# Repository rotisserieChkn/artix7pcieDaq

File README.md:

## About

WORK IN PROGRESS

Right now, only the KiCAD pcb files have been added to the repo. The HDL and PC side software used to communicate with the PCB over PCIe have not been added yet. Stay tuned!

## Licensing

This repository contains hardware, software, and HDL components
that are licensed separately.

### Hardware

All original hardware design files in the `hardware/`
directory are licensed under the CERN Open Hardware
License Version 2 - Weakly Reciprocal (CERN-OHL-W-2.0).

### Software and HDL

All original firmware source code in the `software/` and `hdl/`
directories are licensed under the Mozilla Public License
2.0 (MPL-2.0).

### Third-party components

Third-party components retain their respective original
licenses. See their accompanying license notices where
applicable.

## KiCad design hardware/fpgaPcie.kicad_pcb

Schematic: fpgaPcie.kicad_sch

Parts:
C1, C7, C9, C23, C26, C32, C33, C54: 1210_47uF; C_1210_3225Metric
C2, C4, C6, C8, C13, C15, C19, C22, C24, C29, C31: 0603_100nF; C_0603_1608Metric
C3, C5, C14, C17, C30: 1210_10uF; C_1210_3225Metric
C10, C11, C12, C16, C18, C20, C21, C25, C27, C28: 0402_100nF; R_0402_1005Metric
C34, C35, C36, C39, C40, C41, C44, C45, C46, C49, C50, C51, C57, C58, C59, C60, C61, C62, C65, C66, C68, C70, C73, C74, C76, C77, C78: 0603_470nF; C_0603_1608Metric
C37, C38, C42, C43, C47, C48, C52, C53, C55, C56, C63, C64, C67, C69, C71, C72: 0805_4.7uF; C_0805_2012Metric
C75: 0603_50pF; C_0603_1608Metric
D1, D2, D3, D4: LED_0805; LED_0805_2012Metric
J1: PJ-002AH; MFG_PN PJ-002AH
J2: 6pinJTAG; PinHeader_1x06_P2.54mm_Vertical
J3: jumper_header; PinHeader_1x02_P2.54mm_Vertical
J4: jumper_header; 2x2_Header_100mil
J6: Bus_PCI_Express_x4; BUS_PCIexpress_x4
J7: TL3305AF260QG
J10: SMA_Connector; EMPCB.CSMAFSTJ.A
R1, R2, R8, R23, R24, R25, R26, R27, R34, R58, R60, R61, R62, R63: 0603_2k2; R_0603_1608Metric
R3, R4, R5, R6, R7, R14, R17, R30, R33, R38, R43, R51, R52, R64, R65: 0603_100R; R_0603_1608Metric
R9, R10, R20, R22, R28, R31, R41, R42, R48: 0603_10k; R_0603_1608Metric
R11, R12: 0603_6.65k; R_0603_1608Metric
R13, R15, R32, R35, R36, R45, R46: 0603_330k; R_0603_1608Metric
R16, R19, R40: 0603_71.5K; R_0603_1608Metric
R18, R21, R39, R53, R56: 0603_3.3K; R_0603_1608Metric
R29: 0603_20k; R_0603_1608Metric
R37, R47: 0603_34.8K; R_0603_1608Metric
R44, R66, R69: 0603_45.3k; R_0603_1608Metric
R49: 0603_220R; R_0603_1608Metric
R50: 0603_49R9; R_0603_1608Metric
R54: 0603_100k; R_0603_1608Metric
R55, R57: 0603_402R; R_0603_1608Metric
R59: RA_res_0603; R_0603_RA
R67: 0603_1k; R_0603_1608Metric
TP1: test_point; TP
U1, U2, U4, U5, U7: TPSM843521; QFN_FCMOD_9; MFG_PN TPSM843521RCJR
U3: XC7A35T-CSG325; Xilinx_CSG325; MFG_PN XC7A35T-CSG325
U6: 128MBIT-NOR; SOIC-16W_7.5x10.3mm_P1.27mm; MFG_PN S25FL128SAGMFI003
U8: 100MHz; ASEM1-100.000MHZ-LC-T; MFG_PN ASEM1-100.000MHZ-LC-T
U9: ADC3908S025; VQFN-32-1EP_4x4mm_P0.4mm_EP2.8x2.8mm_MODDED_PASTE; MFG_PN ADC3908S025IRSMT
U10: TPS7A2018PDBVR; SOT-23-5; MFG_PN TPS7A2018PDBVR
U11: THS4541IRGTR; VQFN-16-1EP_3x3mm_P0.5mm_EP1.45x1.45mm_CUSTOM_PASTE; MFG_PN THS4541IRGTR
X1: ECS-2520MV-200-CN-TR; 50_MHz_OSC; MFG_PN ECS-2520MV-200-CN-TR

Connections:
1V0_MGTAVCC: C8.1, C9.1, C56.1, C65.1, C66.1, C67.1, R12.2, U2.4 (VOUT), U3.B4 (MGTAVCC), U3.C5 (MGTAVCC), U3.E5 (MGTAVCC), U3.F5 (MGTAVCC)
1V0_VCCINT: C6.1, C7.1, C49.1, C50.1, C51.1, C52.1, C54.1, C60.1, C69.1, R11.2, U1.4 (VOUT), U3.F7 (VCCINT), U3.F9 (VCCINT), U3.F11 (VCCBRAM), U3.G8 (VCCINT), U3.G10 (VCCBRAM), U3.H7 (VCCINT), U3.H9 (VCCINT), U3.H11 (VCCBRAM), U3.J8 (VCCINT), U3.J12 (VCCINT), U3.K7 (VCCINT), U3.K11 (VCCINT), U3.L8 (VCCINT), U3.L12 (VCCINT), U3.M7 (VCCINT), U3.M11 (VCCINT), U3.N8 (VCCINT), U3.N10 (VCCINT), U3.N12 (VCCINT), U3.P9 (VCCINT), U3.P11 (VCCINT)
1V2_MGTAVTT: C24.1, C26.1, C61.1, C62.1, C63.1, C64.1, R31.2, R51.1, U3.A2 (MGTAVTT), U3.C1 (MGTAVTT), U3.E1 (MGTAVTT), U3.F3 (MGTAVTT), U3.G2 (MGTAVTT), U5.4 (VOUT)
1V8_ADC: C72.1, C73.1, C76.1, R58.1, U9.12 (AVDD), U9.13 (AVDD), U9.16 (M0), U10.5 (VOUT), X1.4 (VDD)
1V8_VCCAUX: C22.1, C23.1, C53.1, C55.1, C57.1, C58.1, C59.1, R29.2, U3.G12 (VCCAUX), U3.H13 (VCCAUX), U3.J10 (VCCADC_0), U3.K13 (VCCAUX), U3.M13 (VCCAUX), U3.P13 (VCCAUX), U4.4 (VOUT)
3V3_VCCIO: C1.1, C19.1, C31.1, C32.1, C33.1, C34.1, C35.1, C36.1, C37.1, C38.1, C39.1, C40.1, C41.1, C42.1, C43.1, C44.1, C45.1, C46.1, C47.1, C48.1, C68.1, C70.1, C71.1, C74.1, C77.1, J2.6 (VCC), R1.2, R2.2, R23.2, R24.2, R25.2, R26.2, R27.2, R34.2, R44.2, R49.2, U3.A16 (VCCO_15), U3.B13 (VCCO_15), U3.C10 (VCCO_15), U3.D17 (VCCO_15), U3.E10 (VCCO_0), U3.E12 (CFGBVS_0), U3.E14 (VCCO_15), U3.G18 (VCCO_15), U3.H15 (VCCO_15), U3.L6 (VCCO_34), U3.L16 (VCCO_14), U3.M3 (VCCO_34), U3.P7 (VCCO_34), U3.P17 (VCCO_14), U3.R4 (VCCO_34), U3.R10 (VCCO_0), U3.R14 (VCCO_14), U3.T1 (VCCO_34), U3.T11 (VCCO_14), U3.U8 (VCCO_14), U3.U18 (VCCO_14), U3.V5 (VCCO_34), U3.V15 (VCCO_14), U6.2 (VCC), U7.4 (VOUT), U8.4 (VDD), U9.27 (IOVDD), U10.1 (VIN), U10.3 (ENA), U11.5 (VS+), U11.6 (VS+), U11.7 (VS+), U11.8 (VS+), U11.12 (~PD); also elsewhere on the board
12V_VIN: C2.1, C3.1, C4.1, C5.1, C13.1, C14.1, C15.1, C17.1, C29.1, C30.1, J1.1, R9.2, R10.2, R28.2, U1.6 (VIN), U2.6 (VIN), U4.6 (VIN), U5.6 (VIN), U7.6 (VIN)
/ADC_CLK_GEN: R59.1, U3.N18 (IO_L10P_T1_D14_14)
/ADC_D0: U3.C14 (IO_L9P_T1_DQS_AD3P_15), U9.32 (D0)
/ADC_D1: U3.B15 (IO_L9N_T1_DQS_AD3N_15), U9.31 (D1)
/ADC_D2: U3.B14 (IO_L10P_T1_AD11P_15), U9.26 (D2)
/ADC_D3: U3.A15 (IO_L10N_T1_AD11N_15), U9.25 (D3)
/ADC_D4: U3.D13 (IO_L11P_T1_SRCC_15), U9.24 (D4)
/ADC_D5: U3.C13 (IO_L11N_T1_SRCC_15), U9.23 (D5)
/ADC_D6: U3.E13 (IO_L12P_T1_MRCC_15), U9.22 (D6)
/ADC_D7: U3.D14 (IO_L12N_T1_MRCC_15), U9.21 (D7)
/ADC_IN_N: C75.1, R4.2, R67.1, U9.11 (INAM)
/ADC_IN_P: C75.2, R52.2, R67.2, U9.10 (INAP)
/ADC_RESET: R69.1, U3.A9 (IO_L3N_T0_DQS_AD1N_15)
/AMP_IN_N: R53.2, R55.1, U11.3 (IN-)
/AMP_IN_P: R56.2, R57.1, U11.2 (IN+)
/AMP_OUT_N: R4.1, U11.11 (OUT-)
/AMP_OUT_P: R52.1, U11.10 (OUT+)
/CONFIG_RESET: J7.1, J7.2, R25.1, U3.P10 (PROGRAM_B_0)
/M0: R1.1, U3.R12 (M0_0); also elsewhere on the board
/M1: R8.2, U3.R11 (M1_0); also elsewhere on the board
/M2: J3.1 (A), R2.1, U3.F13 (M2_0); also elsewhere on the board
/MGTAVCC_PG: R10.1, R21.2, U2.8 (SS/PG), U5.1 (EN)
/PCIE_REFCLKB_N: C11.1, U3.D5 (MGTREFCLK0N_216)
/PCIE_REFCLKB_P: C10.1, U3.D6 (MGTREFCLK0P_216)
/PCIE_REFCLKC_N: C11.2, J6.A14 (REFCLK-)
/PCIE_REFCLKC_P: C10.2, J6.A13 (REFCLK+)
/PCIE_RX0_N: J6.B15 (PETn0), U3.E3 (MGTPRXN0_216)
/PCIE_RX0_P: J6.B14 (PETp0), U3.E4 (MGTPRXP0_216)
/PCIE_RX1_N: J6.B20 (PETn1), U3.A3 (MGTPRXN1_216)
/PCIE_RX1_P: J6.B19 (PETp1), U3.A4 (MGTPRXP1_216)
/PCIE_RX2_N: J6.B24 (PETn2), U3.C3 (MGTPRXN2_216)
/PCIE_RX2_P: J6.B23 (PETp2), U3.C4 (MGTPRXP2_216)
/PCIE_RX3_N: J6.B28 (PETn3), U3.G3 (MGTPRXN3_216)
/PCIE_RX3_P: J6.B27 (PETp3), U3.G4 (MGTPRXP3_216)
/PCIE_TX0_N: C16.1, U3.H1 (MGTPTXN0_216)
/PCIE_TX0_P: C12.1, U3.H2 (MGTPTXP0_216)
/PCIE_TX1_N: C20.1, U3.F1 (MGTPTXN1_216)
/PCIE_TX1_P: C18.1, U3.F2 (MGTPTXP1_216)
/PCIE_TX2_N: C25.1, U3.D1 (MGTPTXN2_216)
/PCIE_TX2_P: C21.1, U3.D2 (MGTPTXP2_216)
/PCIE_TX3_N: C28.1, U3.B1 (MGTPTXN3_216)
/PCIE_TX3_P: C27.1, U3.B2 (MGTPTXP3_216)
/PCIE_UX0_N: C16.2, J6.A17 (PERn0)
/PCIE_UX0_P: C12.2, J6.A16 (PERp0)
/PCIE_UX1_N: C20.2, J6.A22 (PERn1)
/PCIE_UX1_P: C18.2, J6.A21 (PERp1)
/PCIE_UX2_N: C25.2, J6.A26 (PERn2)
/PCIE_UX2_P: C21.2, J6.A25 (PERp2)
/PCIE_UX3_N: C28.2, J6.A30 (PERn3)
/PCIE_UX3_P: C27.2, J6.A29 (PERp3)
/QSPI_CS: R34.1, U3.L15 (IO_L6P_T0_FCS_B_14), U6.7 (CS#)
/QSPI_DQ0: R30.2, U3.K16 (IO_L1P_T0_D00_MOSI_14)
/QSPI_DQ1: R33.2, U3.L17 (IO_L1N_T0_D01_DIN_14)
/QSPI_DQ2: R38.2, U3.J15 (IO_L2P_T0_D02_14)
/QSPI_DQ3: R43.2, U3.J16 (IO_L2N_T0_D03_14)
/QSPI_SCK: R50.2, U3.E8 (CCLK_0), U6.16 (SCK); also elsewhere on the board
/TCK: R7.1, U3.F8 (TCK_0)
/TCK_JTAG: J2.4 (TCK), R7.2
/TDI: R5.1, U3.T9 (TDI_0)
/TDI_JTAG: J2.2 (TDI), R5.2
/TDO: R6.1, U3.T8 (TDO_0)
/TDO_JTAG: J2.3 (TDO), R6.2
/TMS: R3.1, U3.R8 (TMS_0)
/TMS_JTAG: J2.1 (TMS), R3.2
/VCCAUX_PG: R28.1, R39.2, U4.8 (SS/PG), U7.1 (EN)
/VCCINT_PG: R9.1, R18.2, U1.8 (SS/PG), U4.1 (EN)
/VCM: C78.1, U9.7 (VCM), U11.9 (VOCM)
/~PCIE_PERST: R17.1, U3.M14 (IO_L8P_T1_D11_14)
/~PCIE_WAKE: R14.1, U3.M17 (IO_L7N_T1_D10_14)
GND: C1.2, C2.2, C3.2, C4.2, C5.2, C6.2, C7.2, C8.2, C9.2, C13.2, C14.2, C15.2, C17.2, C19.2, C22.2, C23.2, C24.2, C26.2, C29.2, C30.2, C31.2, C32.2, C33.2, C34.2, C35.2, C36.2, C37.2, C38.2, C39.2, C40.2, C41.2, C42.2, C43.2, C44.2, C45.2, C46.2, C47.2, C48.2, C49.2, C50.2, C51.2, C52.2, C53.2, C54.2, C55.2, C56.2, C57.2, C58.2, C59.2, C60.2, C61.2, C62.2, C63.2, C64.2, C65.2, C66.2, C67.2, C68.2, C69.2, C70.2, C71.2, C72.2, C73.2, C74.2, C76.2, C77.2, C78.2, D1.1, D2.1, D3.1, D4.1, J1.2, J1.3, J2.5 (GND), J3.2 (B), J6.A4 (GND), J6.A12 (GND), J6.A15 (GND), J6.A18 (GND), J6.A20 (GND), J6.A23 (GND), J6.A24 (GND), J6.A27 (GND), J6.A28 (GND), J6.A31 (GND), J6.B4 (GND), J6.B7 (GND), J6.B13 (GND), J6.B16 (GND), J6.B18 (GND), J6.B21 (GND), J6.B22 (GND), J6.B25 (GND), J6.B26 (GND), J6.B29 (GND), J6.B32 (GND), J7.3, J7.4, J10.2, R8.1, R13.1, R15.1, R16.1, R18.1, R19.1, R20.1, R21.1, R22.1, R32.1, R35.1, R36.1, R37.1, R39.1, R40.1, R41.1, R42.1, R45.1, R46.1, R47.1, R48.1, R54.2, R56.1, R66.1, U1.3 (GND), U2.3 (GND), U3.A1 (GND), U3.A5 (GND), U3.A7 (GND), U3.A8 (GND), U3.A11 (GND), U3.A18 (GND), U3.B3 (GND), U3.B7 (GND), U3.B8 (GND), U3.B18 (GND), U3.C2 (GND), U3.C6 (GND), U3.C7 (GND), U3.C15 (GND), U3.D3 (GND), U3.D4 (GND), U3.D7 (GND), U3.D12 (GND), U3.E2 (GND), U3.E6 (GND), U3.E7 (GND), U3.E9 (GND), U3.E11 (VCCBATT_0), U3.F4 (GND), U3.F6 (GND), U3.F10 (GND), U3.F16 (GND), U3.G1 (GND), U3.G5 (GND), U3.G6 (GND), U3.G7 (GND), U3.G9 (GND), U3.G11 (GND), U3.G13 (GND), U3.H3 (GND), U3.H4 (GND), U3.H5 (GND), U3.H6 (GND), U3.H8 (GND), U3.H10 (GND), U3.H12 (GND), U3.J1 (GND), U3.J2 (GND), U3.J3 (GND), U3.J7 (GND), U3.J9 (GNDADC_0), U3.J11 (GND), U3.J13 (GND), U3.J17 (GND), U3.K4 (GND), U3.K8 (GND), U3.K9 (VREFN_0), U3.K10 (VP_0), U3.K12 (GND), U3.K14 (GND), U3.L1 (GND), U3.L7 (GND), U3.L9 (VN_0), U3.L10 (VREFP_0), U3.L11 (GND), U3.L13 (GND), U3.M8 (GND), U3.M9 (DXN_0), U3.M10 (DXP_0), U3.M12 (GND), U3.M18 (GND), U3.N5 (GND), U3.N7 (GND), U3.N9 (GND), U3.N11 (GND), U3.N13 (GND), U3.N15 (GND), U3.P2 (GND), U3.P8 (GND), U3.P12 (GND), U3.R9 (GND), U3.T6 (GND), U3.T16 (GND), U3.U3 (GND), U3.U13 (GND), U3.V1 (GND), U3.V10 (GND), U3.V18 (GND), U4.3 (GND), U5.3 (GND), U6.10 (VSS), U7.3 (GND), U8.2 (GND), U9.6 (PDN), U9.19 (M2), U9.28 (DGND), U9.33 (GND), U10.2 (GND), U11.13 (VS-), U11.14 (VS-), U11.15 (VS-), U11.16 (VS-), U11.17 (~PD), X1.2 (GND); also elsewhere on the board
unnamed: D1.2, R60.2
unnamed: D2.2, R61.2
unnamed: D3.2, R62.2
unnamed: D4.2, R63.2
unnamed: J4.2, J6.B17 (~PRSNT2)
unnamed: J4.4, J6.B31 (~PRSNT2)
unnamed: J6.A11 (~PERST), R17.2
unnamed: J4.1, J4.3, J6.A1 (~PRSNT1)
unnamed: J6.B11 (~WAKE), R14.2
unnamed: J10.1, R53.1, R54.1
unnamed: R11.1, R20.2, U1.2 (FB)
unnamed: R13.2, U1.7 (MODE)
unnamed: R16.2, U1.9 (RT/SYNC)
unnamed: R12.1, R22.2, U2.2 (FB)
unnamed: R15.2, U2.7 (MODE)
unnamed: R19.2, U2.9 (RT/SYNC)
unnamed: R50.1, U3.K18 (IO_L3N_T0_DQS_EMCCLK_14)
unnamed: R49.1, U3.J18 (IO_L3P_T0_DQS_PUDC_B_14)
unnamed 94: U3.A12 (IO_L7N_T1_AD2N_15); also elsewhere on the board
unnamed 95: U3.B12 (IO_L7P_T1_AD2P_15); also elsewhere on the board
unnamed 96: U3.A14 (IO_L8N_T1_AD10N_15); also elsewhere on the board
unnamed 97: U3.A13 (IO_L8P_T1_AD10P_15); also elsewhere on the board
unnamed: U3.P14 (IO_L12P_T1_MRCC_14), U8.3 (OUT)
unnamed: R65.2, U3.D15 (IO_L13N_T2_MRCC_15)
unnamed: R64.2, U3.E15 (IO_L13P_T2_MRCC_15)
unnamed 101: U3.A17 (IO_L15N_T2_DQS_ADV_B_15); also elsewhere on the board
unnamed 102: U3.B16 (IO_L15P_T2_DQS_15); also elsewhere on the board
unnamed: R60.1, U3.U17 (IO_L16N_T2_A15_D31_14)
unnamed 104: U3.B17 (IO_L16N_T2_A27_15); also elsewhere on the board
unnamed 105: U3.C16 (IO_L16P_T2_A28_15); also elsewhere on the board
unnamed: R61.1, U3.U16 (IO_L17N_T2_A13_D29_14)
unnamed: R63.1, U3.V17 (IO_L18N_T2_A11_D27_14)
unnamed: R62.1, U3.V16 (IO_L18P_T2_A12_D28_14)
unnamed: R51.2, U3.A6 (MGTRREF_216)
unnamed: R23.1, U3.F12 (DONE_0)
unnamed: R24.1, U3.T10 (INIT_B_0)
unnamed: R29.1, R41.2, U4.2 (FB)
unnamed: R35.2, U4.7 (MODE)
unnamed: R37.2, U4.9 (RT/SYNC)
unnamed: R31.1, R42.2, U5.2 (FB)
unnamed: R36.2, U5.7 (MODE)
unnamed: R40.2, U5.9 (RT/SYNC)
unnamed: R32.2, U5.8 (SS/PG)
unnamed: R27.1, R43.1, U6.1 (HOLD#/IO3)
unnamed: R30.1, U6.15 (SI/IO0)
unnamed: R33.1, U6.8 (SO/IO1)
unnamed: R26.1, R38.1, U6.9 (WP#/IO2)
unnamed: R44.1, R48.2, U7.2 (FB)
unnamed: R46.2, U7.7 (MODE)
unnamed: R47.2, U7.9 (RT/SYNC)
unnamed: R45.2, U7.8 (SS/PG)
unnamed: TP1.1, U8.1 (~STBY)
unnamed: R59.3, U9.8 (CLK)
unnamed: R64.1, U9.30 (DCLK)
unnamed: R66.2, U9.18 (M1)
unnamed: R69.2, U9.9 (RESET)
unnamed: R65.1, U9.29 (~DCLK)
unnamed: R55.2, U11.4 (FB+)
unnamed: R57.2, U11.1 (FB-)
unnamed: R58.2, X1.1 (EN)
unnamed: R59.2, X1.3 (OUT)

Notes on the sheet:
Sets Fsw = 1200kHz
Power Rails Needed: VCCINT & VCCBRAM: 1.0V VCCAUX: 1.8V VCCIO: 3.3V MGTAVCC: 1.0V MGTAVTT: 1.2V
*IMPORTANT NOTE* This is NOT the default pcie lane pinout generated by the 7-Series PCIe IP block in AMD Vivado. Go to \*PROJECT_DIR*\pcie_7x_0_ex.gen\sources_1\ip\pcie_7x_0\source/pcie_7x_0-PCIE_X0Y0.xdc Edit these lines to look like this: # PCIe Lane 0 set_property LOC GTPE2_CHANNEL_X0Y3 [get_cel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
Power Sequencing: VCCINT, VCCBRAM, MGTAVCC simultaneously MGTAVTT depends on MGTAVCC VCCAUX depends on VCCINT VCCIO depends on VCCAUX
Sets Fsw = 600kHz
~STBY pulled up internally by default

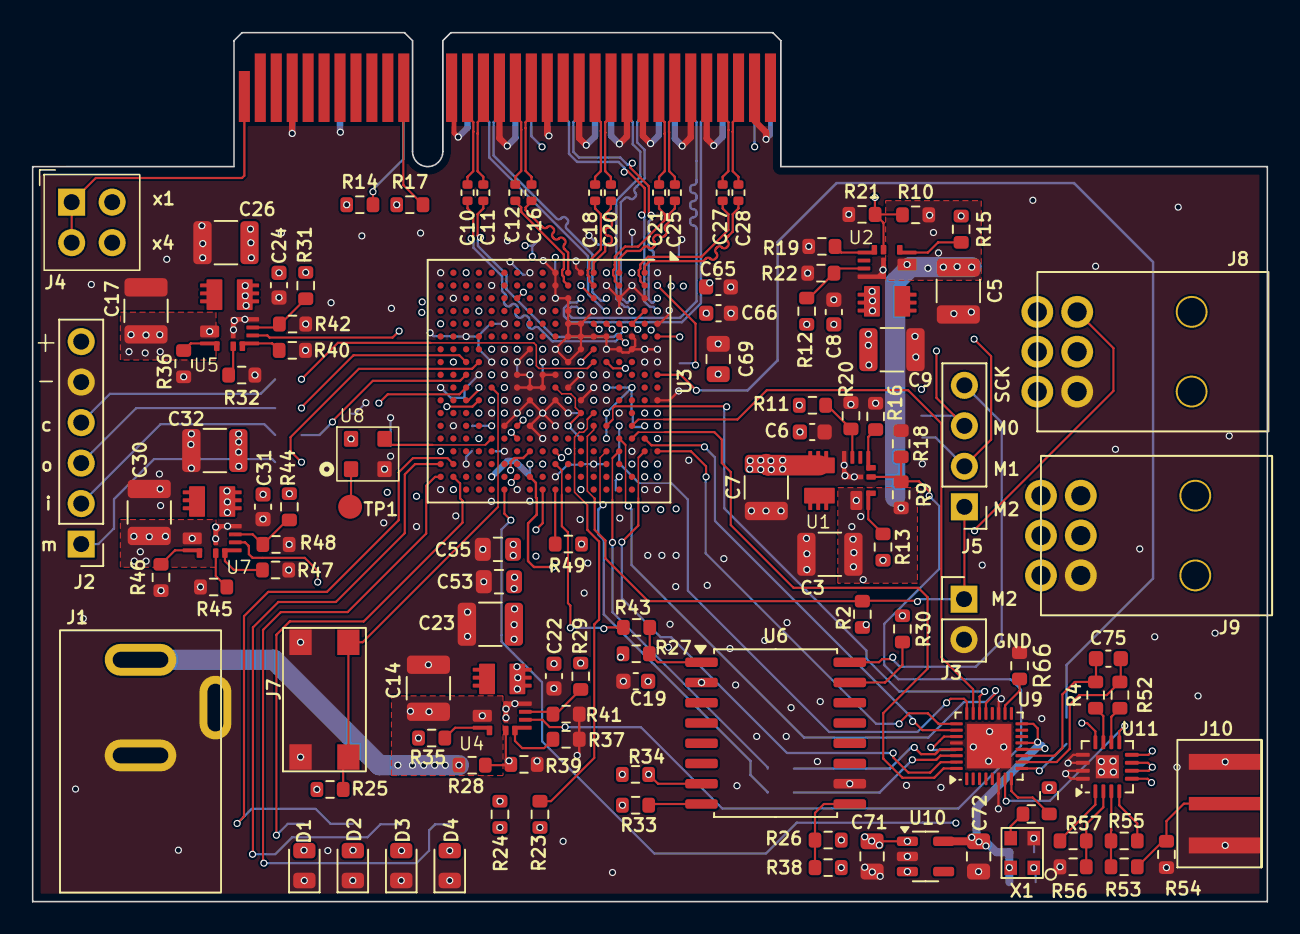
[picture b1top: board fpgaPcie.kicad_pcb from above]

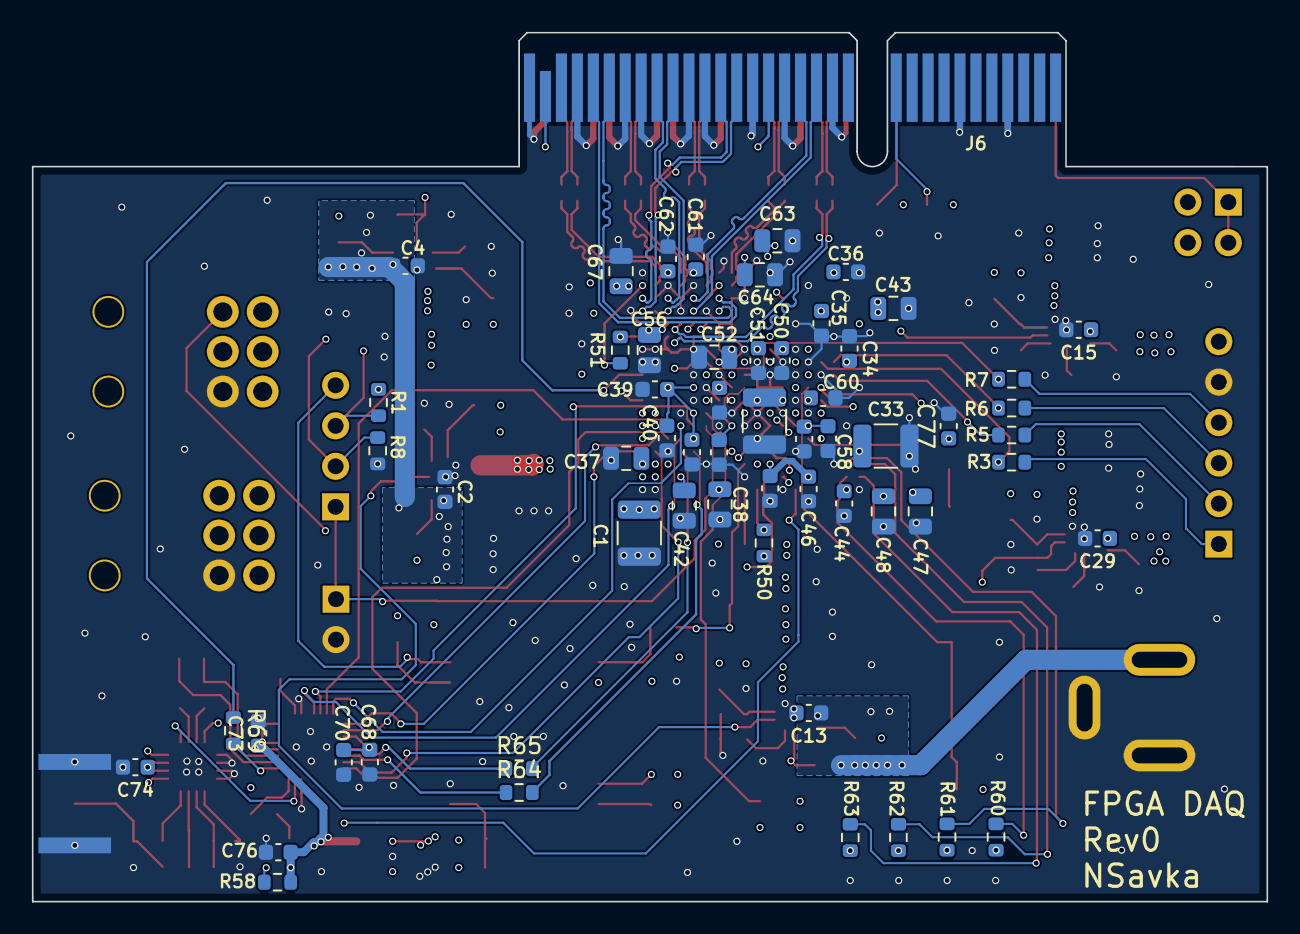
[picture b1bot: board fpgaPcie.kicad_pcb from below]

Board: 6 copper layers, 77.4 x 54.5 mm, 171 parts (60 on the bottom side), 137 nets.

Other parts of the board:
J5: jumper_header; PinHeader_1x04_P2.54mm_Vertical
J8, J9: 1053141106; nanofit_2x3_1053141106

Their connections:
3V3_VCCIO: J8.1, J9.1; also elsewhere on the board
/M0: J5.3; also elsewhere on the board
/M1: J5.2; also elsewhere on the board
/M2: J5.1; also elsewhere on the board
/QSPI_SCK: J5.4; also elsewhere on the board
GND: J8.6, J9.6; also elsewhere on the board
unnamed 94: J8.3; also elsewhere on the board
unnamed 95: J8.2; also elsewhere on the board
unnamed 96: J8.5; also elsewhere on the board
unnamed 97: J8.4; also elsewhere on the board
unnamed 101: J9.3; also elsewhere on the board
unnamed 102: J9.2; also elsewhere on the board
unnamed 104: J9.5; also elsewhere on the board
unnamed 105: J9.4; also elsewhere on the board
